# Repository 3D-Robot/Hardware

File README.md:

This is a project to make a 3D robot that can self replicate itself and make multiple designs.

for more information visit [this link](https://3drobot.engineer).

This project was made with these open-source software:

* Dia

* KiCAD

* FreeCAD

* Git

* NgSPICE

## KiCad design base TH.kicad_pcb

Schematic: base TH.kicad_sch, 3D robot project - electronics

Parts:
A1: Arduino_Nano_v3.x; Arduino_Nano
BT1: Battery_Cell; 282856-8
C1, C2, C5, C8, C9, C10, C13, C16: 100n; R82DCXXXXCK50K
C3, C6, C11, C14: 10u; R82DCXXXXCK50K
C4, C7, C12, C15: 1u; R82DCXXXXCK50K
J1: 282856-8
J2: Raspberry_Pi_2_3; Raspberry pi 4
M1, M2, M3, M4: Stepper_Motor_bipolar; 1-350944-0
R1, R2, R3, R4, R5, R6, R7, R8: 20k; R_Axial_DIN0204_L3.6mm_D1.6mm_P5.08mm_Horizontal
U1, U2, U3, U4: TMC2209 silent step stick
U5: LM2596

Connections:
/5: A1.30 (VIN), C1.1, C2.1, C9.1, C10.1, J2.2 (5V), J2.4 (5V), R1.1, R2.1, R5.1, R6.1, U1.SPREAD, U1.Vio, U2.SPREAD, U2.Vio, U3.SPREAD, U3.Vio, U4.SPREAD, U4.Vio, U5.3 (OUT+)
/+: BT1.1 (+), C3.2, C4.2, C5.2, C6.2, C7.2, C8.2, C11.2, C12.2, C13.2, C14.2, C15.2, C16.2, J1.1, J1.2, J1.3, J1.4, U1.Vm, U2.Vm, U3.Vm, U4.Vm, U5.1 (IN+)
/-: A1.4 (GND), A1.29 (GND), BT1.2 (-), C1.2, C2.2, C3.1, C4.1, C5.1, C6.1, C7.1, C8.1, C9.2, C10.2, C11.1, C12.1, C13.1, C14.1, C15.1, C16.1, J1.5, J1.6, J1.7, J1.8, J2.6 (GND), J2.9 (GND), J2.14 (GND), J2.20 (GND), J2.25 (GND), J2.30 (GND), J2.34 (GND), J2.39 (GND), R3.1, R4.1, R7.1, R8.1, U1.En, U1.GND, U1.MS1, U1.MS2, U1.PDN/UART, U2.En, U2.GND, U2.MS1, U2.MS2, U2.PDN/UART, U3.En, U3.GND, U3.MS1, U3.MS2, U3.PDN/UART, U4.En, U4.GND, U4.MS1, U4.MS2, U4.PDN/UART, U5.2 (IN-), U5.4 (OUT-)
/M11: M1.1, U1.A1
/M12: M1.2 (-), U1.A2
/M13: M1.3, U1.B1
/M14: M1.4, U1.B2
/M21: M2.1, U2.A1
/M22: M2.2 (-), U2.A2
/M23: M2.3, U2.B1
/M24: M2.4, U2.B2
/M31: M3.1, U3.A1
/M32: M3.2 (-), U3.A2
/M33: M3.3, U3.B1
/M34: M3.4, U3.B2
/M41: M4.1, U4.A1
/M42: M4.2 (-), U4.A2
/M43: M4.3, U4.B1
/M44: M4.4, U4.B2
/dir_1: A1.5 (D2), U1.DIR
/dir_2: A1.6 (D3), U2.DIR
/dir_3: A1.7 (D4), U3.DIR
/dir_4: A1.8 (D5), U4.DIR
/step_1: A1.9 (D6), U1.STEP
/step_2: A1.10 (D7), U2.STEP
/step_3: A1.11 (D8), U3.STEP
/step_4: A1.12 (D9), U4.STEP
unnamed: R1.2, R3.2, U1.Vref
unnamed: R2.2, R4.2, U2.Vref
unnamed: R5.2, R7.2, U3.Vref
unnamed: R6.2, R8.2, U4.Vref

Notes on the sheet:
silent VS dynamic
blue can be configured by arduino...
single 4 batteries input(8 pins)
micro steps {

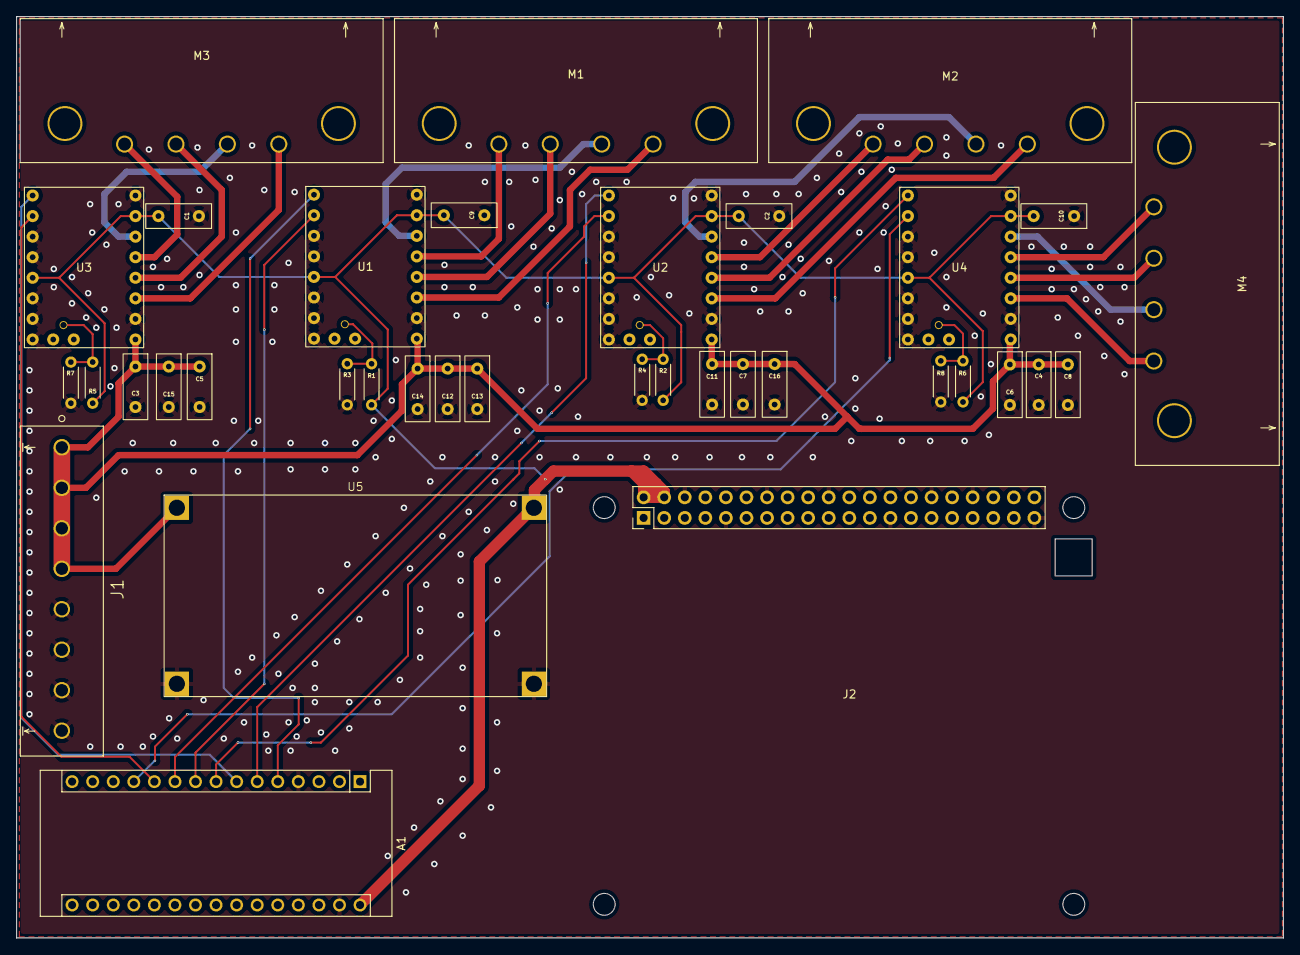
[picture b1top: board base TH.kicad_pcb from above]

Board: 2 copper layers, 156.5 x 113.8 mm, 36 parts (0 on the bottom side), 31 nets.

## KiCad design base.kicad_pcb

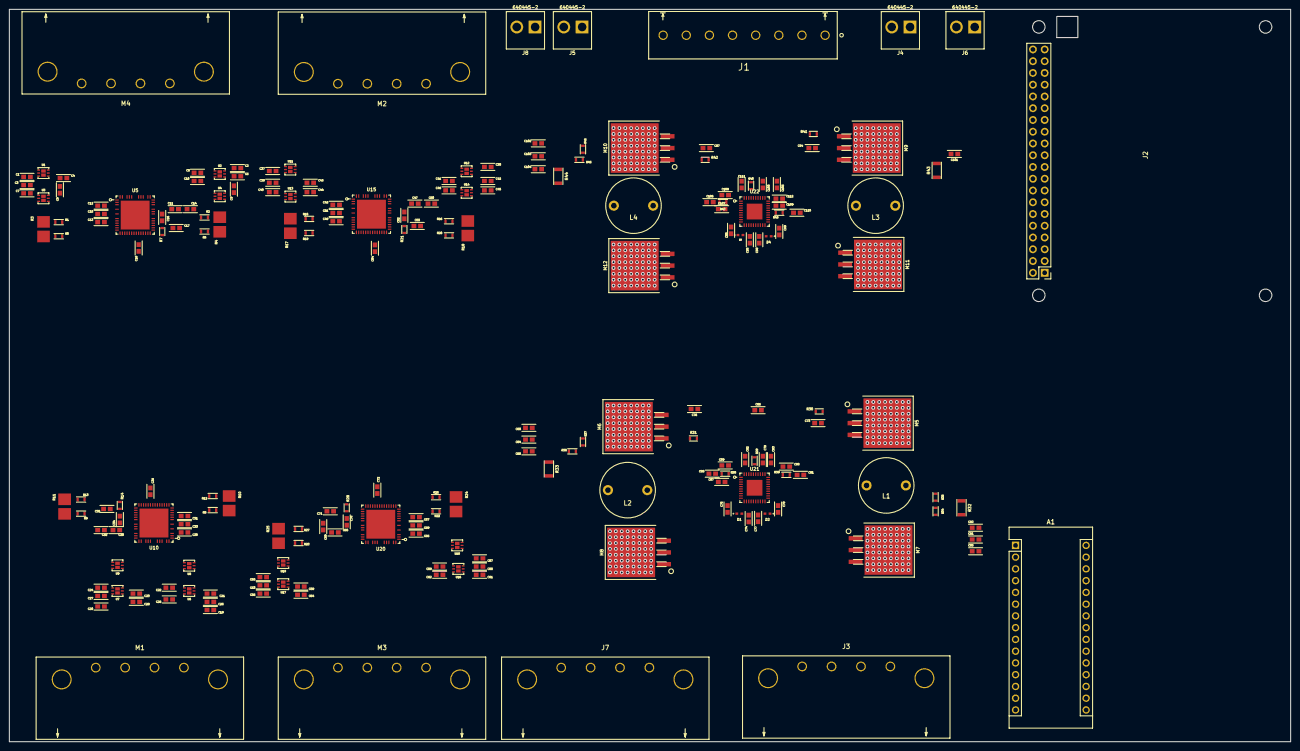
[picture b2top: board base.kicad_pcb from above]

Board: 2 copper layers, 276.9 x 158.2 mm, 211 parts (0 on the bottom side), 169 nets, no tracks yet.

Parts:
A1: Arduino_Nano_v3.x; Arduino_Nano
C1, C2, C19, C20, C37, C38, C55, C56, C102: 4.7u; C0603X105J4RACTU
C3, C4, C5, C6, C14, C21, C22, C23, C24, C32, C39, C40, C41, C42, C50, C57, C58, C59, C60, C68, C81, C84, C103: 220n; C0603X105J4RACTU
C7, C8, C9, C10, C25, C26, C27, C28, C43, C44, C45, C46, C61, C62, C63, C64: 1n; C0603X105J4RACTU
C11, C15, C18, C29, C33, C36, C47, C51, C54, C65, C69, C72, C75, C78, C96, C99: 100n; C0603X105J4RACTU
C12, C13, C30, C31, C48, C49, C66, C67, C74, C77, C95, C98: 2.2u; C0603X105J4RACTU
C16, C34, C52, C70, C80, C85, C104: 22n; C0603X105J4RACTU
C17, C35, C53, C71: 470n; C0603X105J4RACTU
C73, C76, C82, C83, C94, C97: 10u; C0603X105J4RACTU
C79, C100: 1u; C0603X105J4RACTU
C86: 120u; C0603X105J4RACTU
C87: 3.3n; C0603X105J4RACTU
C88, C90: 10p; C0603X105J4RACTU
C89, C108: 120n; C0603X105J4RACTU
C91, C110: 3.3nF; C0603X105J4RACTU
C92, C111: 2.2uF; C0603X105J4RACTU
C93, C112: 120nF; C0603X105J4RACTU
C101: 47u; C0603X105J4RACTU
C105: 22u; C0603X105J4RACTU
C106: 4.7n; C0603X105J4RACTU
C107: 15p; C0603X105J4RACTU
C109: 15pF; C0603X105J4RACTU
D1, D2, D3, D4: RB161QS-40; RB161QS-40T18R
J1: 282856-8
J2: Raspberry_Pi_2_3; Raspberry pi 4
J3, J7: 1-350944-0
J4, J5, J6, J8: 640445-2
L1, L2: 2.2u; SBC9-2R2-792
L3: 3.3u; SBC9-2R2-792
L4: 6.8u; SBC9-2R2-792
M1, M2, M3, M4: Stepper_Motor_bipolar; 1-350944-0
M5, M6, M7, M8, M9, M10, M11, M12: CSD18510KTTT
R1, R2, R5, R6, R8, R9, R12, R13, R15, R16, R19, R20, R22, R23, R26, R27: 47; MCR03EZPFX
R3, R4, R10, R11, R17, R18, R24, R25: 82m; GMR50HJBFWR082
R7, R14, R21, R28: MCR03EZPFL
R29, R40: 19.6k; MCR03EZPFX
R30, R31, R41, R42: 2.2; MCR03EZPFL
R32, R33: 7m; UCR18EVH
R34, R35: 118k; MCR03EZPFX
R36, R37: 10.4k; MCR03EZPFX
R38, R39: 6.81k; MCR03EZPFX
R43: 12m; UCR18EVH
R44: 15m; UCR18EVH
R45: 215k; MCR03EZPFX
R46: 11.3k; MCR03EZPFX
R47: 6.19k; MCR03EZPFX
R48: 8.87K; MCR03EZPFX
U1, U2, U3, U4, U6, U7, U8, U9, U11, U12, U13, U14, U16, U17, U18, U19: UT6K3; UT6K3TCR
U5, U10, U15, U20: TMC5160-WA
U21, U22: LM5143; LM5143RHAR

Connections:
/5: A1.30 (VIN), C101.2, J2.2 (5V), J2.4 (5V), J4.1, J6.1, R43.2, U22.6 (VCCX), U22.26 (VOUT1)
/7.4L: C83.2, C84.2, C85.2, J7.1, J7.2, R33.1, R35.2, U21.5 (VOUT2)
/7.4R: C80.2, C81.2, C82.2, J3.1, J3.2, R32.2, R34.2, U21.26 (VOUT1)
/12: C102.2, C103.2, C104.2, J5.1, J8.1, R44.1, R45.2, U22.5 (VOUT2)
/+: C1.1, C2.2, C11.2, C14.1, C15.2, C19.1, C20.2, C29.2, C32.1, C33.2, C37.1, C38.2, C47.2, C50.1, C51.2, C55.1, C56.2, C65.2, C68.1, C69.2, C73.2, C76.2, C86.2, C94.2, C97.2, C105.2, J1.1, J1.2, J1.3, J1.4, M5.2 (D), M6.2 (D), M9.2 (D), M10.2 (D), U1.3 (D_{2}), U1.6 (D_{1}), U2.3 (D_{2}), U2.6 (D_{1}), U5.5 (VSA), U5.33 (VS), U6.3 (D_{2}), U6.6 (D_{1}), U7.3 (D_{2}), U7.6 (D_{1}), U10.5 (VSA), U10.33 (VS), U11.3 (D_{2}), U11.6 (D_{1}), U12.3 (D_{2}), U12.6 (D_{1}), U15.5 (VSA), U15.33 (VS), U16.3 (D_{2}), U16.6 (D_{1}), U17.3 (D_{2}), U17.6 (D_{1}), U20.5 (VSA), U20.33 (VS), U21.25 (VIN), U21.31 (EN1), U21.40 (EN2), U22.25 (VIN), U22.31 (EN1), U22.40 (EN2)
/-: A1.4 (GND), A1.29 (GND), C1.2, C2.1, C7.2, C8.2, C9.2, C10.2, C12.1, C13.1, C14.2, C15.1, C17.2, C18.1, C19.2, C20.1, C25.2, C26.2, C27.2, C28.2, C30.1, C31.1, C32.2, C33.1, C35.2, C36.1, C37.2, C38.1, C43.2, C44.2, C45.2, C46.2, C48.1, C49.1, C50.2, C51.1, C53.2, C54.1, C55.2, C56.1, C61.2, C62.2, C63.2, C64.2, C66.1, C67.1, C68.2, C69.1, C71.2, C72.1, C73.1, C74.1, C76.1, C77.1, C79.2, C80.1, C81.1, C82.1, C83.1, C84.1, C85.1, C86.1, C87.1, C88.1, C89.1, C90.1, C91.1, C92.1, C93.1, C94.1, C95.1, C97.1, C98.1, C100.2, C101.1, C102.1, C103.1, C104.1, C105.1, C106.1, C107.1, C108.1, C109.1, C110.1, C111.1, C112.1, J1.5, J1.6, J1.7, J1.8, J2.6 (GND), J2.9 (GND), J2.14 (GND), J2.20 (GND), J2.25 (GND), J2.30 (GND), J2.34 (GND), J2.39 (GND), J3.3, J3.4, J4.2, J5.2, J6.2, J7.3, J7.4, J8.2, M7.3 (S), M8.3 (S), M11.3 (S), M12.3 (S), R3.1, R4.1, R5.2, R6.1, R10.1, R11.1, R12.2, R13.1, R17.1, R18.1, R19.2, R20.1, R24.1, R25.1, R26.2, R27.1, R29.1, R36.1, R37.1, R40.1, R46.1, U5.7 (GNDA), U5.13 (CLK), U5.25 (GNDD), U5.48, U10.7 (GNDA), U10.13 (CLK), U10.25 (GNDD), U10.48, U15.7 (GNDA), U15.13 (CLK), U15.25 (GNDD), U15.48, U20.7 (GNDA), U20.13 (CLK), U20.25 (GNDD), U20.48, U21.6 (VCCX), U21.14 (PGND2), U21.17 (PGND1), U21.34 (MODE), U21.35 (AGND), U21.41 (EPAD), U22.14 (PGND2), U22.17 (PGND1), U22.28 (FB1), U22.34 (MODE), U22.35 (AGND), U22.41 (EPAD)
/Buck converter 5 and 12/COMP1: C109.2, R48.1, U22.29 (COMP1)
/Buck converter 5 and 12/COMP2: C107.2, R47.1, U22.2 (COMP2)
/Buck converter 5 and 12/CS1: L3.2, R43.1, U22.27 (CS1)
/Buck converter 5 and 12/CS2: L4.1, R44.2, U22.4 (CS2)
/Buck converter 5 and 12/DEMB: C111.2, U22.33 (DEMB), U22.36 (VDDA), U22.38 (DITH)
/Buck converter 5 and 12/FB2: R45.1, R46.2, U22.3 (FB2)
/Buck converter 5 and 12/HB1: C99.2, D4.1 (N), U22.20 (HB1)
/Buck converter 5 and 12/HB2: C96.2, D3.1 (N), U22.11 (HB2)
/Buck converter 5 and 12/HO1: R41.1, U22.22 (HO1)
/Buck converter 5 and 12/HO2: R42.2, U22.9 (HO2)
/Buck converter 5 and 12/HOL1: M9.1 (G), R41.2, U22.23 (HOL1)
/Buck converter 5 and 12/HOL2: M10.1 (G), R42.1, U22.8 (HOL2)
/Buck converter 5 and 12/LO1: M11.1 (G), U22.18 (LO1), U22.19 (LOL1)
/Buck converter 5 and 12/LO2: M12.1 (G), U22.12 (LOL2), U22.13 (LO2)
/Buck converter 5 and 12/SS1: C112.2, U22.30 (SS1)
/Buck converter 5 and 12/SS2: C108.2, U22.1 (SS2)
/Buck converter 5 and 12/SW1: C99.1, L3.1, M9.3 (S), M11.2 (D), U22.21 (SW1)
/Buck converter 5 and 12/SW2: C96.1, L4.2, M10.3 (S), M12.2 (D), U22.10 (SW2)
/Buck converter 5 and 12/VCC: C95.2, C98.2, D3.2, D4.2, U22.15 (VCC), U22.16 (VCC)
/Buck converter 7.4/COMP1: C90.2, R39.1, U21.29 (COMP1)
/Buck converter 7.4/COMP2: C88.2, R38.1, U21.2 (COMP2)
/Buck converter 7.4/CS1: L1.2, R32.1, U21.27 (CS1)
/Buck converter 7.4/CS2: L2.1, R33.2
/Buck converter 7.4/DEMB: C92.2, U21.33 (DEMB), U21.36 (VDDA), U21.38 (DITH)
/Buck converter 7.4/FB1: R34.1, R36.2, U21.28 (FB1)
/Buck converter 7.4/FB2: R35.1, R37.2, U21.3 (FB2)
/Buck converter 7.4/HB1: C78.2, D2.1 (N), U21.20 (HB1)
/Buck converter 7.4/HB2: C75.2, D1.1 (N), U21.11 (HB2)
/Buck converter 7.4/HO1: R30.1, U21.22 (HO1)
/Buck converter 7.4/HO2: R31.2, U21.9 (HO2)
/Buck converter 7.4/HOL1: M5.1 (G), R30.2, U21.23 (HOL1)
/Buck converter 7.4/HOL2: M6.1 (G), R31.1, U21.8 (HOL2)
/Buck converter 7.4/LO1: M7.1 (G), U21.18 (LO1), U21.19 (LOL1)
/Buck converter 7.4/LO2: M8.1 (G), U21.4 (CS2), U21.12 (LOL2), U21.13 (LO2)
/Buck converter 7.4/SS1: C93.2, U21.30 (SS1)
/Buck converter 7.4/SS2: C89.2, U21.1 (SS2)
/Buck converter 7.4/SW1: C78.1, L1.1, M5.3 (S), M7.2 (D), U21.21 (SW1)
/Buck converter 7.4/SW2: C75.1, L2.2, M6.3 (S), M8.2 (D), U21.10 (SW2)
/Buck converter 7.4/VCC: C74.2, C77.2, D1.2, D2.2, U21.15 (VCC), U21.16 (VCC)
/stepper and controller6/1: C21.2, C25.1, M1.1, U6.1 (S_{1}), U8.6 (D_{1}), U10.1 (BMB1)
/stepper and controller6/2: C22.1, C26.1, M1.2 (-), U6.4 (S_{2}), U8.3 (D_{2}), U10.45 (BMB2)
/stepper and controller6/3: C23.1, C28.1, M1.3, U7.1 (S_{1}), U9.6 (D_{1}), U10.40 (BMA1)
/stepper and controller6/4: C24.1, C27.1, M1.4, U7.4 (S_{2}), U9.3 (D_{2}), U10.37 (BMA2)
/stepper and controller6/CA1: C23.2, U10.42 (CA1)
/stepper and controller6/CA2: C24.2, U10.35 (CA2)
/stepper and controller6/CB1: C21.1, U10.3 (CB1)
/stepper and controller6/CB2: C22.2, U10.43 (CB2)
/stepper and controller6/Digital voltage: C36.2, U10.20 (VCC_IO)
/stepper and controller6/HA1: U7.2 (G_{1}), U10.41 (HA1)
/stepper and controller6/HA2: U7.5 (G_{2}), U10.36 (HA2)
/stepper and controller6/HB1: U6.2 (G_{1}), U10.2 (HB1)
/stepper and controller6/HB2: U6.5 (G_{2}), U10.44 (HB2)
/stepper and controller6/LA1: U9.2 (G_{1}), U10.39 (LA1)
/stepper and controller6/LA2: U9.5 (G_{2}), U10.38 (LA2)
/stepper and controller6/LB1: U8.2 (G_{1}), U10.47 (LB1)
/stepper and controller6/LB2: U8.5 (G_{2}), U10.46 (LB2)
/stepper and controller6/SRAH: R9.2, U10.9 (SRAH)
/stepper and controller6/SRAL: R13.2, U10.8 (SRAL)
/stepper and controller6/SRBH: R8.1, U10.10 (SRBH)
/stepper and controller6/SRBL: R12.1, U10.11 (SRBL)
/stepper and controller6/temp: C31.2, R14.1, U10.6 (5VOUT)
/stepper and controller7/1: C39.2, C43.1, M2.1, U11.1 (S_{1}), U13.6 (D_{1}), U15.1 (BMB1)
/stepper and controller7/2: C40.1, C44.1, M2.2 (-), U11.4 (S_{2}), U13.3 (D_{2}), U15.45 (BMB2)
/stepper and controller7/3: C41.1, C46.1, M2.3, U12.1 (S_{1}), U14.6 (D_{1}), U15.40 (BMA1)
/stepper and controller7/4: C42.1, C45.1, M2.4, U12.4 (S_{2}), U14.3 (D_{2}), U15.37 (BMA2)
/stepper and controller7/CA1: C41.2, U15.42 (CA1)
/stepper and controller7/CA2: C42.2, U15.35 (CA2)
/stepper and controller7/CB1: C39.1, U15.3 (CB1)
/stepper and controller7/CB2: C40.2, U15.43 (CB2)
/stepper and controller7/Digital voltage: C54.2, U15.20 (VCC_IO)
/stepper and controller7/HA1: U12.2 (G_{1}), U15.41 (HA1)
/stepper and controller7/HA2: U12.5 (G_{2}), U15.36 (HA2)
/stepper and controller7/HB1: U11.2 (G_{1}), U15.2 (HB1)
/stepper and controller7/HB2: U11.5 (G_{2}), U15.44 (HB2)
/stepper and controller7/LA1: U14.2 (G_{1}), U15.39 (LA1)
/stepper and controller7/LA2: U14.5 (G_{2}), U15.38 (LA2)
/stepper and controller7/LB1: U13.2 (G_{1}), U15.47 (LB1)
/stepper and controller7/LB2: U13.5 (G_{2}), U15.46 (LB2)
/stepper and controller7/SRAH: R16.2, U15.9 (SRAH)
/stepper and controller7/SRAL: R20.2, U15.8 (SRAL)
/stepper and controller7/SRBH: R15.1, U15.10 (SRBH)
/stepper and controller7/SRBL: R19.1, U15.11 (SRBL)
/stepper and controller7/temp: C49.2, R21.1, U15.6 (5VOUT)
/stepper and controller8/1: C3.2, C7.1, M4.1, U1.1 (S_{1}), U3.6 (D_{1}), U5.1 (BMB1)
/stepper and controller8/2: C4.1, C8.1, M4.2 (-), U1.4 (S_{2}), U3.3 (D_{2}), U5.45 (BMB2)
/stepper and controller8/3: C5.1, C10.1, M4.3, U2.1 (S_{1}), U4.6 (D_{1}), U5.40 (BMA1)
/stepper and controller8/4: C6.1, C9.1, M4.4, U2.4 (S_{2}), U4.3 (D_{2}), U5.37 (BMA2)
/stepper and controller8/CA1: C5.2, U5.42 (CA1)
/stepper and controller8/CA2: C6.2, U5.35 (CA2)
/stepper and controller8/CB1: C3.1, U5.3 (CB1)
/stepper and controller8/CB2: C4.2, U5.43 (CB2)
/stepper and controller8/Digital voltage: C18.2, U5.20 (VCC_IO)
/stepper and controller8/HA1: U2.2 (G_{1}), U5.41 (HA1)
/stepper and controller8/HA2: U2.5 (G_{2}), U5.36 (HA2)
/stepper and controller8/HB1: U1.2 (G_{1}), U5.2 (HB1)
/stepper and controller8/HB2: U1.5 (G_{2}), U5.44 (HB2)
/stepper and controller8/LA1: U4.2 (G_{1}), U5.39 (LA1)
/stepper and controller8/LA2: U4.5 (G_{2}), U5.38 (LA2)
/stepper and controller8/LB1: U3.2 (G_{1}), U5.47 (LB1)
/stepper and controller8/LB2: U3.5 (G_{2}), U5.46 (LB2)
/stepper and controller8/SRAH: R2.2, U5.9 (SRAH)
/stepper and controller8/SRAL: R6.2, U5.8 (SRAL)
/stepper and controller8/SRBH: R1.1, U5.10 (SRBH)
/stepper and controller8/SRBL: R5.1, U5.11 (SRBL)
/stepper and controller8/temp: C13.2, R7.1, U5.6 (5VOUT)
/stepper and controller9/1: C57.2, C61.1, M3.1, U16.1 (S_{1}), U18.6 (D_{1}), U20.1 (BMB1)
/stepper and controller9/2: C58.1, C62.1, M3.2 (-), U16.4 (S_{2}), U18.3 (D_{2}), U20.45 (BMB2)
/stepper and controller9/3: C59.1, C64.1, M3.3, U17.1 (S_{1}), U19.6 (D_{1}), U20.40 (BMA1)
/stepper and controller9/4: C60.1, C63.1, M3.4, U17.4 (S_{2}), U19.3 (D_{2}), U20.37 (BMA2)
/stepper and controller9/CA1: C59.2, U20.42 (CA1)
/stepper and controller9/CA2: C60.2, U20.35 (CA2)
/stepper and controller9/CB1: C57.1, U20.3 (CB1)
/stepper and controller9/CB2: C58.2, U20.43 (CB2)
/stepper and controller9/Digital voltage: C72.2, U20.20 (VCC_IO)
/stepper and controller9/HA1: U17.2 (G_{1}), U20.41 (HA1)
/stepper and controller9/HA2: U17.5 (G_{2}), U20.36 (HA2)
/stepper and controller9/HB1: U16.2 (G_{1}), U20.2 (HB1)
/stepper and controller9/HB2: U16.5 (G_{2}), U20.44 (HB2)
/stepper and controller9/LA1: U19.2 (G_{1}), U20.39 (LA1)
/stepper and controller9/LA2: U19.5 (G_{2}), U20.38 (LA2)
/stepper and controller9/LB1: U18.2 (G_{1}), U20.47 (LB1)
/stepper and controller9/LB2: U18.5 (G_{2}), U20.46 (LB2)
/stepper and controller9/SRAH: R23.2, U20.9 (SRAH)
/stepper and controller9/SRAL: R27.2, U20.8 (SRAL)
/stepper and controller9/SRBH: R22.1, U20.10 (SRBH)
/stepper and controller9/SRBL: R26.1, U20.11 (SRBL)
/stepper and controller9/temp: C67.2, R28.1, U20.6 (5VOUT)
unnamed: C11.1, U5.34 (VCP)
unnamed: C12.2, U5.4 (12VOUT)
unnamed: C16.1, U5.32 (CPI)
unnamed: C16.2, U5.31 (CPO)
unnamed: C17.1, R7.2, U5.30 (VCC)
unnamed: C29.1, U10.34 (VCP)
unnamed: C30.2, U10.4 (12VOUT)
unnamed: C34.1, U10.32 (CPI)
unnamed: C34.2, U10.31 (CPO)
unnamed: C35.1, R14.2, U10.30 (VCC)
unnamed: C47.1, U15.34 (VCP)
unnamed: C48.2, U15.4 (12VOUT)
unnamed: C52.1, U15.32 (CPI)
unnamed: C52.2, U15.31 (CPO)
unnamed: C53.1, R21.2, U15.30 (VCC)
unnamed: C65.1, U20.34 (VCP)
unnamed: C66.2, U20.4 (12VOUT)
unnamed: C70.1, U20.32 (CPI)
unnamed: C70.2, U20.31 (CPO)
unnamed: C71.1, R28.2, U20.30 (VCC)
unnamed: C79.1, U21.32 (RES)
unnamed: C87.2, R38.2
unnamed: C91.2, R39.2
unnamed: C100.1, U22.32 (RES)
unnamed: C106.2, R47.2
unnamed: C110.2, R48.2
unnamed: R1.2, R3.2, U3.1 (S_{1}), U3.4 (S_{2})
unnamed: R2.1, R4.2, U4.1 (S_{1}), U4.4 (S_{2})
unnamed: R8.2, R10.2, U8.1 (S_{1}), U8.4 (S_{2})
unnamed: R9.1, R11.2, U9.1 (S_{1}), U9.4 (S_{2})
unnamed: R15.2, R17.2, U13.1 (S_{1}), U13.4 (S_{2})
unnamed: R16.1, R18.2, U14.1 (S_{1}), U14.4 (S_{2})
unnamed: R22.2, R24.2, U18.1 (S_{1}), U18.4 (S_{2})
unnamed: R23.1, R25.2, U19.1 (S_{1}), U19.4 (S_{2})
unnamed: R29.2, U21.37 (RT)
unnamed: R40.2, U22.37 (RT)

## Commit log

2022-06-06 made README a markdown file
2022-06-12 On branch main modified: README.md adding some details about the project
2022-06-14 add software names
2022-06-17 3D robot electronics
    add the v0.9 design
2022-06-17 Add files via upload
    add v0.9 of the design
2022-06-20 reference designator added
2022-06-25 just dividing the schematics into parts to make individual PCBs
2022-06-25 updating schematics
2022-06-25 changing some capacitors
2022-07-03 base schematic and PCB made
2022-07-04 exporting 3D models
2022-07-23 minor changes
2022-07-27 make a TH version of the base PCB for testing purposes...
2022-07-29 stitching updated
